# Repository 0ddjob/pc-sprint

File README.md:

# PC-SPRINT

- [Clueless Engineer] - the original board is too wide for the Model 5155 (Portable PC) and Model 5160 (PC/XT) due to the presence of Slot 8 and the keyboard socket, so re-designed using SMD for the passives to shrink the width to 24mm (from the original 29.21mm) ... looks like it should fit (but to be tested)
- [Vintage Support Services] - additional designs that shrink the board even further, including one for the Model 4860 (PCjr)

## Navigating This Document

This README has become somewhat unwieldy, so here's an index.

- [Introduction to PC-SPRINT](#introduction-to-pc-sprint) - A quick introduction to the device and how it works.
  - [YouTube Video](#youtube-video) - A YouTube video for those who aren't keen on reading
- [Original File Listing](#original-file-listing) - The original design and accompanying files as released by Doug Severson in 1985.
- [Retro Canada KiCAD Files](#retro-canada-kicad-files) - KiCAD and gerber files drawn up by [VCFed Forum](http://www.vcfed.org/forum/forum.php) user "Retro Canada" for PCB fabrication.
- [My Own "Retro Canada" Board](#my-own-retro-canada-board) - I had a PCB fabricated and assembled it using the above files.
  - [My Testing](#my-testing) - Notes from my own tests with this board.
  - [My Benchmarks](#my-benchmarks) - Benchmarking results.
    - [Landmark](#landmark) - Results from the Landmark benchmarking tool. 
	- [TOPBENCH](#topbench) - Results from the TOPBENCH benchmarking tool.
	- [CheckIt](#checkit) - Results from the CheckIt diagnostic / benchmarking tool.
	- [MIPS](#mips) - You guessed it. Results from the MIPS benchmarking tool.
	- [Benchmarking Conclusions](#benchmarking-conclusions) - Conclusions on benchmark results.
- [Everything Else](#everything-else) - Other interesting documentation and bits and bobs.
- [License](#license) - Licensing information for this project and documentation.

## Introduction to PC-SPRINT

The PC-SPRINT is a DIY PC accelerator board design released by Doug Severson in 1985 and given away for free in computer magazines and on BBSes of the time. It is designed to allow overclocking of an [Intel 8088](Datasheets/Intel%208088%20Datasheet.pdf)-based computer such as the IBM 5150 / 5155 / 5160 PCs, PCjr, Tandy 1000, Compaq Portable<sup>*</sup>, and I'm sure a whole lot more.

It is highly recommended that the CPU be upgraded to an [NEC V20](https://en.wikipedia.org/wiki/NEC_V20) or equivalent, as the standard 8088 shipped with these early machines will probably not run at clock speeds over the original 4.77MHz. Also the 8087 co-processor, if fitted, will need to be a higher clocked version.

<sup>*</sup> The PC-SPRINT has now been tested with a Compaq Portable 1 and works great! There are a few things to bear in mind which are referenced in [issue #1](/../../issues/1). Many thanks to @cognitivegears for the excellent feedback.

In these machines and other contemporary "PC Compatibles" the system clock is usually generated by a 14.318MHz crystal connected to an [Intel 8284A](Datasheets/Intel%208284A-1%20Datasheet.pdf) Clock Generator Driver. The 8284A divides the crystal's signal by 3 giving us our 4.77MHz clock. Unfortunately we can't just replace the crystal on the motherboard as this would play havoc with all sorts of things. The basis of this accelerator is to provide an additional, faster crystal coupled with an additional 8284A to generate a faster clock signal that will be used exclusively by the CPU.

The PC-SPRINT also adds a "Turbo" switch as found on later PCs to enable / disable the higher clock rate and a hardware reset button, which is lacking on the IBM 5150. The included [WARMBOOT.COM](WARMBOOT.COM) utility sets a BIOS flag which skips the RAM test on a warm boot, making the reset very fast even at stock speed.

When the PC-SPRINT is built with the designer's recommended 22.11MHz crystal the CPU will run at a clock speed of 7.37MHz giving an impressive 64% processing speed increase (on paper). Faster speeds may be possible with faster crystals but were not recommended for stability reasons. Note that in order to utilise this accelerator the original 4.77MHz 8088 CPU must be replaced with either a faster version of the same CPU (e.g. 8088-2) or equivalent clone (e.g. [NEC V20](https://en.wikipedia.org/wiki/NEC_V20), which is highly recommended as it brings other benefits).

Much more information is available in the [original documentation](PCSPRINT.DOC) ([PDF](PCSPRINT.DOC.PDF)).

### YouTube Video

I have now also put together a short introductory video. Unfortunately it can't be embedded here, so please click the image below to be taken to YouTube:

## Original File Listing

Here is a rough index of the files included with the package as originally distributed:

- [1STREAD.ME](1STREAD.ME) - Listing of project files (you're reading a modern adaptation of this)
- [ARTWRK1X.BOT](ARTWRK1X.BOT) - Bottom layer printed circuit artwork 1x size (obsolete printer format) ([PDF](ARTWRK1X.BOT.PDF))
- [ARTWRK1X.TOP](ARTWRK1X.TOP) - Top layer printed circuit artwork 1x size (obsolete printer format) ([PDF](ARTWRK1X.TOP.PDF))
- [ARTWRK2X.BOT](ARTWRK2X.BOT) - Bottom layer printed circuit artwork 2x size (obsolete printer format) ([PDF](ARTWRK2X.BOT.PDF))
- [ARTWRK2X.TOP](ARTWRK2X.TOP) - Top layer printed circuit artwork 2x size (obsolete printer format) ([PDF](ARTWRK2X.TOP.PDF))
- [FEEDTHRU](FEEDTHRU) - Top - bottom "feed through" connection diagram ([PDF](FEEDTHRU.PDF))
- [NOPRTYCK.COM](NOPRTYCHK.COM) - Program to disable parity checks
- [PARTLIST](PARTLIST) - Parts list & placement drawing ([PDF](PARTLIST.PDF))
- [PCSPRINT.BAT](PCSPRINT.BAT) - Batch file to print PC-SPRINT info & drawings 
- **[PCSPRINT.DOC](PCSPRINT.DOC) - Description & construction info ([PDF](PCSPRINT.DOC.PDF))**
- [SCHEMATC](SCHEMATC) - Electronic circuit diagram ([PDF](SCHEMATC.PDF))
- [WARMBOOT.COM](WARMBOOT.COM) - Program to set "warm boot" flag

Note that some files have PDF conversions which were included with the version of the package as received by myself, so I have also linked those above.

The author was keen to include the original unmodified package of files with future revisions, so it is available in [pcsprint_1985.zip](References/pcsprint_1985.zip).

## Retro Canada KiCAD Files

A Vintage Computer Federation forum user by the name of Retro Canada [redrew the original PCB design in KiCAD](http://www.vcfed.org/forum/showthread.php?60803-I-overclocked-my-IBM-5150) and [released the files freely](https://sites.google.com/site/tandycocoloco/dropbox/PC-SPRINT.zip) on November 26th 2017.

I have added a mirror of this KiCAD project [here](Retro%20Canada/PC-SPRINT.zip). The package includes gerber files so KiCAD is not required if you are planning on sending the files directly to a PCB fabricator.

The user built their own based on these files (pictured above - [more of their pictures here](Retro%20Canada/Images)) but could only get it to run reliably up to a 17.43MHz crystal (CPU clock speed 5.81MHz). It is believed that this is related to DMA activity and/or RAM speed, however without the rest of their system specs it's hard to be sure.

### My Own "Retro Canada" Board

I also successfully built and tested a PC-SPRINT using Retro Canada's files. I used [PCBWay](https://www.pcbway.com/) for my PCB fabrication. Mine has a 21.47727MHz HC-49S crystal giving a CPU clock speed of 7.16MHz - the same as the popular [Tandy 1000 EX and HX](https://en.wikipedia.org/wiki/Tandy_1000#Tandy_1000_EX_and_HX) machines. Thankfully after extensive testing I haven't run into any of the issues experienced by Retro Canada, even at this higher speed.

I have experimented with 22.11MHz and even 24MHz crystals and encountered stability issues at these speeds, so I recommend starting at 21.47MHz.

#### My Testing

Here are the specs of my IBM 5150 as tested:

|Part|Model|Notes|
|---|---|---|
|CPU|[NEC V20](https://en.wikipedia.org/wiki/NEC_V20)|4.77MHz stock / 7.16MHz "turbo" with PC-SPRINT|
|FPU|[Intel 8087-2](https://en.wikipedia.org/wiki/Intel_8087)|8087 co-processor rated up to 8MHz|
|RAM|640KB|(256KB onboard, 384KB on SixPakPlus card)<sup>*</sup>|
|Motherboard|64-256KB [Later Revision](http://www.minuszerodegrees.net/5150/motherboard/5150_motherboard_revisions.htm)|[10/27/82 BIOS](http://minuszerodegrees.net/5150/bios/5150_bios_revisions.htm)|
|HDD|XT-IDE with 512MB CompactFlash card|Running [IDE_XTP.BIN BIOS](https://www.lo-tech.co.uk/wiki/XTIDE_Universal_BIOS)|
|Graphics|IBM CGA<sup>**</sup>||
|Network|3com EtherLink II||
|Floppy|2x Tandon 360KB 5.25"|Stock IBM Floppy ISA interface|
|PSU|Standard 110VAC / 63.5W|
|Operating System|[IBM PC DOS 2000](https://winworldpc.com/product/pc-dos/2000)||

<sup>\* All RAM chips were recently replaced with "New Old Stock" [Samsung KM4164B-15](http://www.minuszerodegrees.net/memory/4164.htm) parts, which have a 150ns access time.</sup>
<sup>\** I have since upgraded to an IBM EGA card (with RAM expansion) and can confirm that the PC-SPRINT works great with this setup. Benchmarks below use the CGA card.</sup>

I have done extensive testing with the above system and had no problems whatsoever. I was expecting issues with DMA activity as others have reported, however have seen none at all. Perhaps this is due to the XT-IDE and its [unusual handling of DMA](https://www.lo-tech.co.uk/xt-cfv3-dma-transfer-mode/). The PC even boots up fine with the turbo mode engaged. Incidentally, cold boot time is 1:02 stock vs. 43 seconds in turbo mode.

The included NOPRTYCHK and WARMBOOT utilities work exactly as advertised with no issues as does the new reset button.

The picture below shows how I installed the turbo and reset buttons in the case. Both are 12mm panel mount push buttons - the turbo button is a latching version:

### My Benchmarks

I ran through a series of benchmarking applications in both turbo and non-turbo mode.

These screenshots (and the videos on [my YouTube channel](https://www.youtube.com/ctrlaltrees)) were captured with a rather elaborate capture setup involving a [CGA2RGB](https://gglabs.us/node/2063), [OSSC](https://videogameperfection.com/products/open-source-scan-converter/) and a [StarTech USB3HDCAP](https://www.startech.com/uk/AV/Converters/Video/usb-3-0-video-capture-device-hdmi-dvi-vga~USB3HDCAP), but that's a tale for another time.

These benchmarks compare the performance of the NEC V20 CPU in stock 4.77MHz and turbo 7.16MHz modes using the PC-SPRINT. Unfortunately I don't have the original Intel 8088 CPU anymore to be able to test, however for some indication of how this system performs compared to a stock 5150 take a look at the [MIPS](#mips) benchmark below.

With the exception of CheckIt, all of these benchmarking tools were downloaded from the [TOPBENCH Other Benchmarks](https://dosbenchmark.wordpress.com/otherbenchmarks/) page.

#### Landmark

Landmark System Speed Test was released in 1984 by Landmark Research Internation Corporation and was one of the first DOS benchmarking tools. Here I'm using version 6.00, the final release from 1993.

|Benchmark|V20 Stock|V20 Turbo|Improvement|
|---|---|---|---|
|CPU<sup>*</sup>|3.02MHz|4.60MHz|52.32%|
|FPU|4.56MHz|6.92MHZ|51.75%|
|Video|412.35 chr/ms|446.03 chr/ms|8.17%|

<sup>\* The way this figure is calculated is interesting (and generally considered wrong) but the percentage increase is all that matters to us. There is more information on the way Landmark arrives at their CPU figure [here](https://dosbenchmark.wordpress.com/research/landmark/).

#### TOPBENCH

[TOPBENCH](https://dosbenchmark.wordpress.com/) is a modern realtime DOS benchmarking tool. An interesting feature is its "database", which allows you to compare your system's performance to that submitted by other users. I'm using version 0.38 with the full database.

Note that TOPBENCH reports the run times of its tests in microseconds, so a lower score is better (faster).

|Benchmark|V20 Stock|V20 Turbo|Improvement|
|---|---|---|---|
|TOPBENCH Score|5|7|2|
|MemTest|2488μ|1640μ|51.71%|
|MemEA|1863μ|1211μ|53.84%|
|Opcodes|1519μ|991μ|53.28%|
|VidMem|2009μ|1840μ|9.18%|
|3DGames|1408μ|919μ|53.21%|
|Total|9287μ|6601μ|40.69%|

According to the database we've gone from an NCR PC4 to an Olivetti PC-1. As I'm not familiar with either of these machines I guess I'll just have to take their word for it. ;)

#### CheckIt

From [WinWorldPC](https://winworldpc.com/product/checkit/30), who said it better than I ever could:

CheckIt, from TouchStone Software Corporation, is a diagnostic tool for generic PC/XT/AT compatible computers. It can perform tests on RAM, hard disks, video cards, floppy disks, motherboard resources, and I/O devices. It has an easy to use menu interface but can also run tests non-interactively.

I'm running version 3, the last release from 1990. In each of these screenshots the "Stock" value (top grey line) is the NEC V20 with turbo mode off.

|Benchmark|V20 Stock|V20 Turbo|Improvement|
|---|---|---|---|
|CPU [Dhrystones](https://en.wikipedia.org/wiki/Dhrystone)|387|597|54.26%|
|FPU [Whetstones](https://en.wikipedia.org/wiki/Whetstone_(benchmark))|123.1K|186K|51.1%|

|Benchmark|V20 Stock|V20 Turbo|Improvement|
|---|---|---|---|
|Transfer Speed|198.9K/sec|303.2K/sec|52.44%|
|Average Seek Time<sup>*</sup>|1.7ms|1.1ms|54.55%|
|Track Seek Time<sup>*</sup>|1.7ms|1.1ms|54.55%|

<sup>\* Note that when it comes to seek times, lower numbers are better.</sup>

|Benchmark|V20 Stock|V20 Turbo|Improvement|
|---|---|---|---|
|BIOS Video Speed|637chr/sec|968chr/sec|51.96%|
|Direct Video Speed|4837chr/sec|7395chr/sec|52.88%|

I also ran various RAM tests with turbo enabled to see if it would pick up any errors, but all tests passed with no problems.

#### MIPS

Chips & Technologies MIPS was written by Jim Bracking and released in 1986. It's a very comprehensive test covering various number-crunching operations, and even shows your score compared to typical examples of machines of that era - an IBM PC, PC/AT and a Compaq 386.

|Benchmark|V20 Stock|V20 Turbo|Improvement|
|---|---|---|---|
|General Instructions|0.19|0.29|52.63%|
|Integer Instructions|0.32|0.49|53.12%|
|Memory To Memory|0.26|0.41|57.69%|
|Register To Register|0.39|0.60|53.85%|
|Register To Memory|0.33|0.51|54.55%|
|Overall Performance|0.30|0.46|53.33%|

MIPS also shows that our overclocked NEC V20 is over twice as fast as a stock IBM 5150 running an Intel 8088 CPU.

### Benchmarking Conclusions

As we can see, the speedup on all fronts is in the region of 50-55%, which is a massive improvement for around £6 worth of components. According to [MIPS](#mips), with the addition of the V20 and the overclock this machine is now twice as fast as a standard IBM PC. I haven't encountered any stability issues but my testing is ongoing and of course, if I come across them I will document them here.

Finally, of course benchmarks are entirely artificial and don't necessarily reflect real world results. In my testing I have found that, without exception, every single game on this machine (and I have a fair few) is more playable with massively reduced slowdowns and stuttering. That's a hard thing to quantify, however, so with that in mind I am working on a series of comparison videos which should hopefully be available [on my YouTube channel](https://www.youtube.com/ctrlaltrees) soon.

There is now [a general overview of my overclocked IBM 5150 on YouTube](https://youtu.be/Y7NNCWvt1nY) for anyone interested.

### Everything Else

Here I'll collect any other odd bits of info I can find on the PC-SPRINT.

[pcspnt.txt](Everything%20Else/Documents/pcspnt.txt) - PC-SPRINT 1000 by Charles Robertson (1988-08-13). Information relating to the installation of the PC-SPRINT in the Tandy 1000A. \[[source](http://www.oldskool.org/guides/tvdog/documents.html)\]

## License

The PC-SPRINT was originally released with the following licensing conditions:

> License to duplicate, distribute and use PC-SPRINT is hereby granted to individuals, for personal use, and non-profit organizations with the following conditions:
> 
> 1. All files in this package must be distributed intact and unmodified.
> 2. No fees may be charged (other than reasonable duplication costs) for this package or any printed circuit board made by its use.
> 3. All commercial rights to this package remain the property of the author.
> 4. Hobby or user oriented magazines may reprint all or portions of this package, as long as credit is given to the author.
> 5. For-profit organizations may obtain a license by contacting the author.
> 6. The author will not be held liable for any damages or injuries, direct or subsequent, that may result from its distribution, construction, installation or use.

Attempts have been made to track down the author but to no avail, so this project is shared here in good faith that the sentiments of the original designer will be honoured.

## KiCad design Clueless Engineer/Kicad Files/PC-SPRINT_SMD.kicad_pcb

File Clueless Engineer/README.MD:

Experimental SMD version - original version too wide for IBM Model 5155 (Portable PC) and 5160 (PC/XT).<br>

New board width is 24mm, down from original 29.21mm ... let's see if it'll fit ...

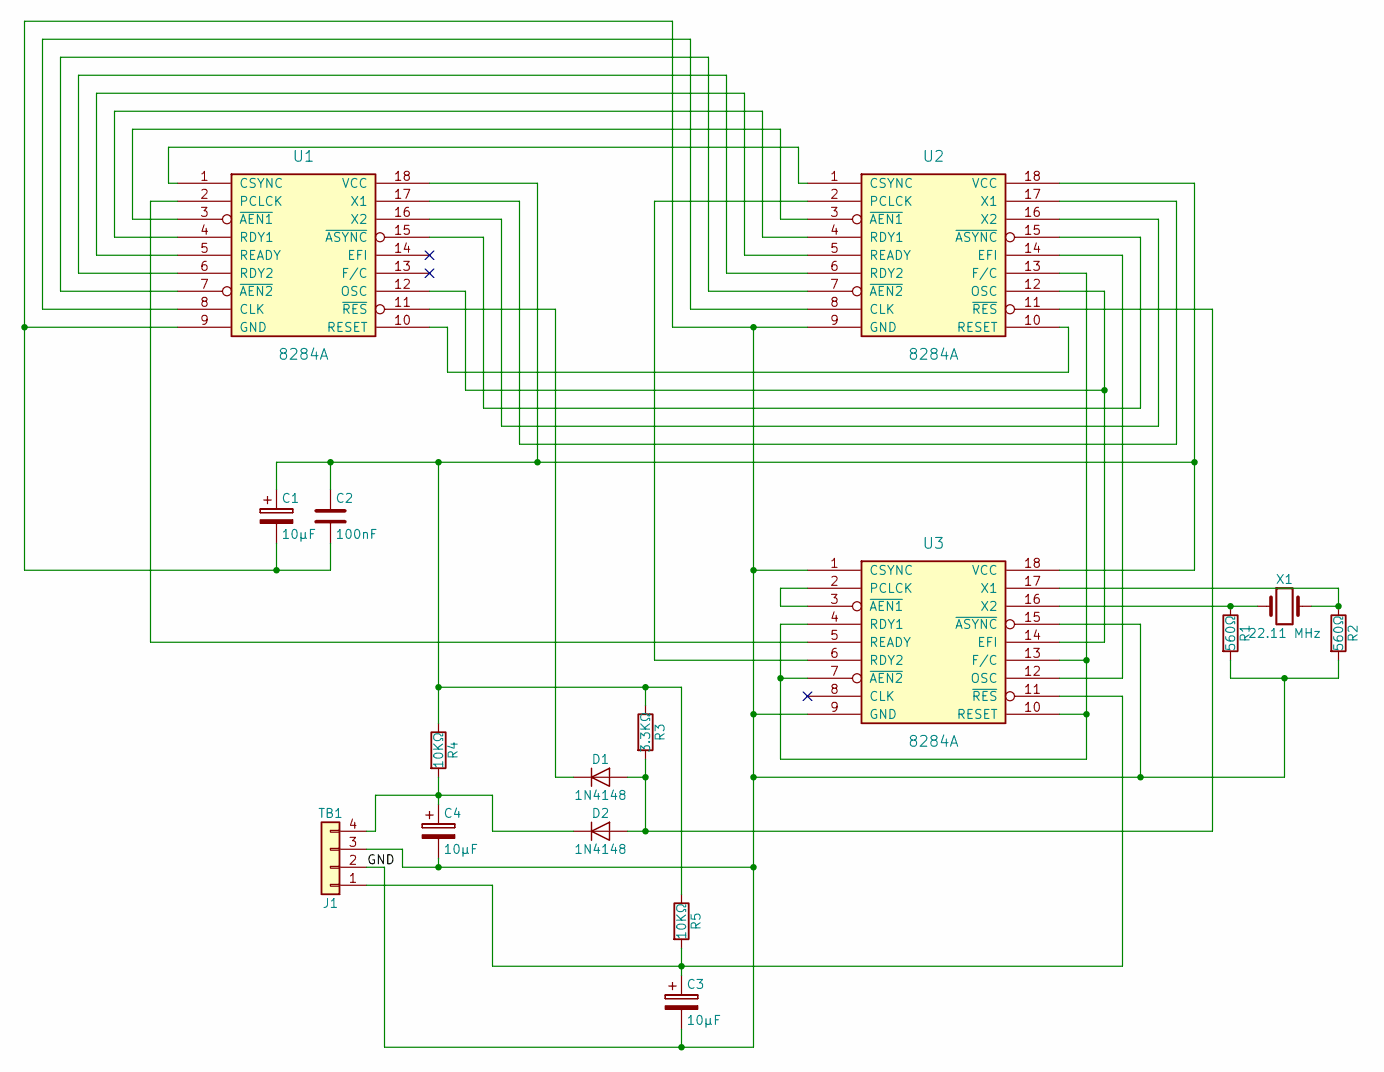
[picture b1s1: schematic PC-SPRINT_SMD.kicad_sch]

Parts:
C1, C3, C4: 10µF; C_1206_3216Metric_Pad1.33x1.80mm_HandSolder
C2: 100nF; C_0805_2012Metric_Pad1.18x1.45mm_HandSolder
D1, D2: 1N4148; D_SOD-123
J1: TB1; PinHeader_1x04_P2.54mm_Vertical
R1, R2: 560Ω; R_0805_2012Metric_Pad1.20x1.40mm_HandSolder
R3: 3.3KΩ; R_0805_2012Metric_Pad1.20x1.40mm_HandSolder
R4, R5: 10KΩ; R_0805_2012Metric_Pad1.20x1.40mm_HandSolder
U1: 8284A; DIP-18_W7.62mm_Socket
U2, U3: 8284A; DIP-18_W7.62mm
X1: 22.11 MHz; Crystal_HC18-U_Vertical

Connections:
/GND: C1.2, C2.2, C3.2, C4.2, J1.2, J1.3, R1.2, R2.2, U1.9 (GND), U2.9 (GND), U3.1 (CSYNC), U3.9 (GND), U3.15 (~ASYNC)
unnamed: D1.2 (A), D2.2 (A), R3.2, U2.11 (~RES)
unnamed: D1.1 (K), U1.11 (~RES)
unnamed: C4.1, D2.1 (K), J1.4, R4.2
unnamed: C3.1, J1.1, R5.2, U3.11 (~RES)
unnamed: U1.8 (CLK), U2.8 (CLK)
unnamed: U1.1 (CSYNC), U2.1 (CSYNC)
unnamed: U1.12 (OSC), U2.12 (OSC), U3.14 (EFI)
unnamed: U1.2 (PCLCK), U3.5 (READY)
unnamed: U1.4 (RDY1), U2.4 (RDY1)
unnamed: U1.6 (RDY2), U2.6 (RDY2)
unnamed: U1.5 (READY), U2.5 (READY)
unnamed: U1.10 (RESET), U2.10 (RESET)
unnamed: C1.1, C2.1, R3.1, R4.1, R5.1, U1.18 (VCC), U2.18 (VCC), U3.18 (VCC)
unnamed: U1.17 (X1), U2.17 (X1)
unnamed: U1.16 (X2), U2.16 (X2)
unnamed: U1.3 (~AEN1), U2.3 (~AEN1)
unnamed: U1.7 (~AEN2), U2.7 (~AEN2)
unnamed: U1.15 (~ASYNC), U2.15 (~ASYNC)
unnamed: U2.14 (EFI), U3.12 (OSC)
unnamed: U2.13 (F/C), U3.4 (RDY1), U3.7 (~AEN2), U3.10 (RESET), U3.13 (F/C)
unnamed: U2.2 (PCLCK), U3.6 (RDY2)
unnamed: U3.2 (PCLCK), U3.3 (~AEN1)
unnamed: R2.1, U3.17 (X1), X1.2
unnamed: R1.1, U3.16 (X2), X1.1

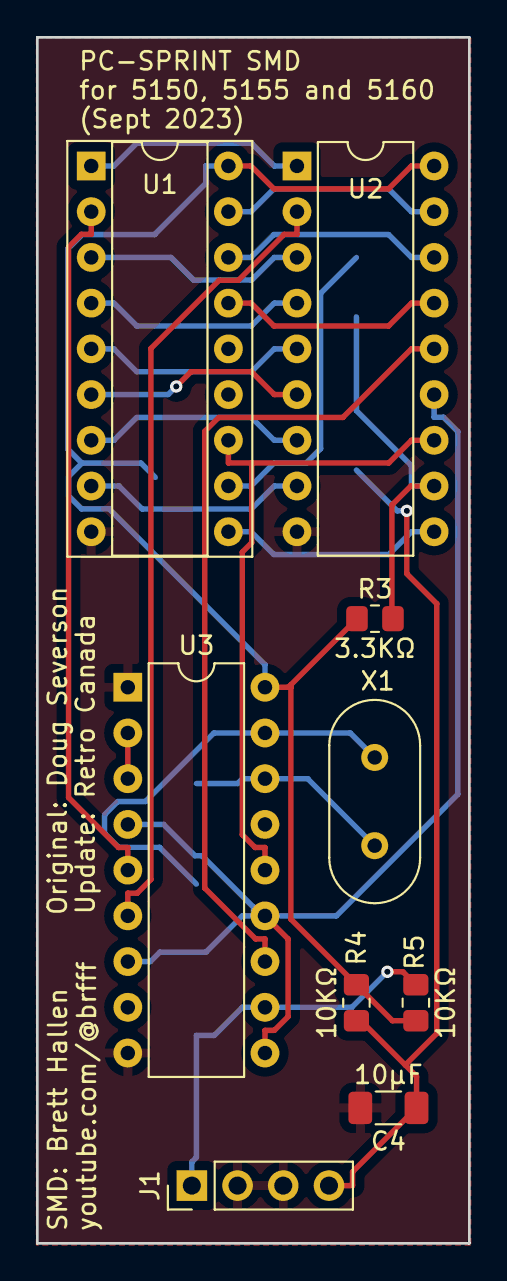
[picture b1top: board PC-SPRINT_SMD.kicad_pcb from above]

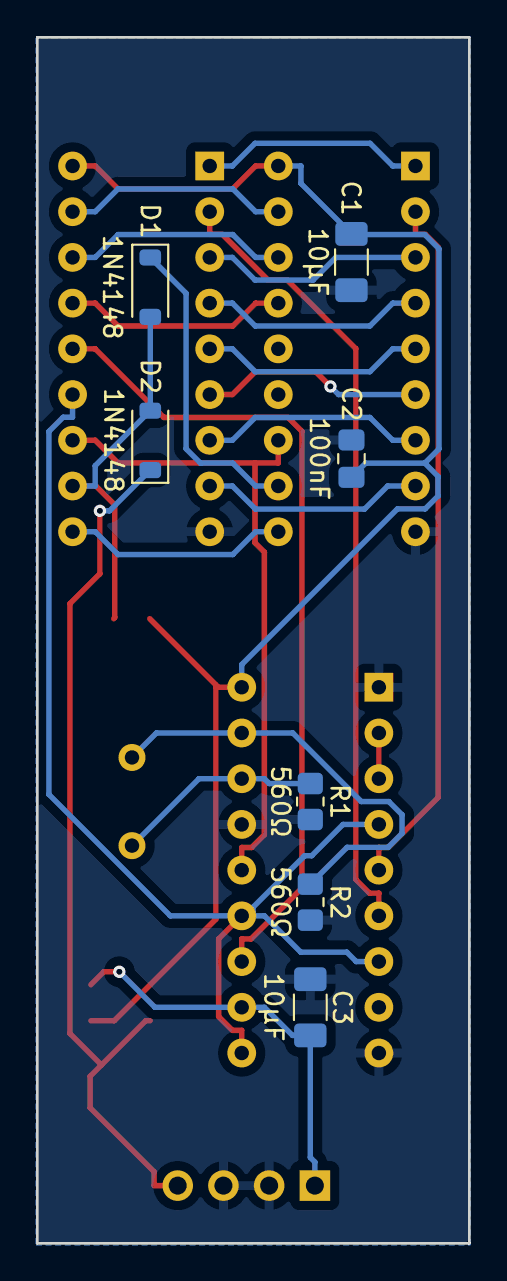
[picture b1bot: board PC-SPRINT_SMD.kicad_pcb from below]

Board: 2 copper layers, 24.0 x 67.0 mm, 16 parts (7 on the bottom side), 25 nets.

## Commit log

2023-08-26 Reduced width of PCB by 2.46mm for IBM Model 5160
2023-08-26 Reduce PCB width by 2.46mm to fit Model 5160
2023-08-27 SMD version
2023-08-27 Kicad & Gerber files for experimental SMD version
    Board is 25mm wide ... hopefully small enough for IBM Model 5155 (Portable PC) and 5160 (PC/XT)
2023-08-27 Mock-up images
2023-08-27 Experimental SMD version to fit IBM Model 5155 & 5160
2023-08-28 Cleaned up main folder
    Moved original design files to own folder
2023-08-28 Corrected original width
2023-08-28 Additional skinny designs
    One design for the IBM Model 4860 (PCjr) and a super-skinny design for the model 5150/5155/5160
2023-08-28 Create .gitignore
    Annoying macOS .DS_Store files
2023-08-28 Delete .DS_Store
    macOS rubbish
2023-08-28 Added details of new sections
2023-09-06 Shrunk PCB to 24mm (from original 29.1mm)
2023-09-06 Getting PNGs to show in README

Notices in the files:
README.md:
> License to duplicate, distribute and use PC-SPRINT is hereby granted to individuals, for personal use, and non-profit organizations with the following conditions:
> 1. All files in this package must be distributed intact and unmodified.
> 2. No fees may be charged (other than reasonable duplication costs) for this package or any printed circuit board made by its use.
> 3. All commercial rights to this package remain the property of the author.
> 4. Hobby or user oriented magazines may reprint all or portions
